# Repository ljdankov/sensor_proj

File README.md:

# sensor_proj
The files in here are designed to pull capacitive touch data (and other relevant sensors) from the boards I have been working with (ESP32 and Teensy 3.2).
Files included
  ARDUINO IDE: Teensy 3.2 version, ARDUINO IDE: ESP32 Version, PYTHON Interface
It should be noted that documentation may be somewhat minimal as this repository is mostly for myself and other people I am working with on project

At minimum, note dependencies in the files. The Teensy variant will need the teensy software from: https://www.pjrc.com/teensy/teensyduino.html
The esp32 variant will require the Arduino IDE software from:
https://github.com/espressif/arduino-esp32

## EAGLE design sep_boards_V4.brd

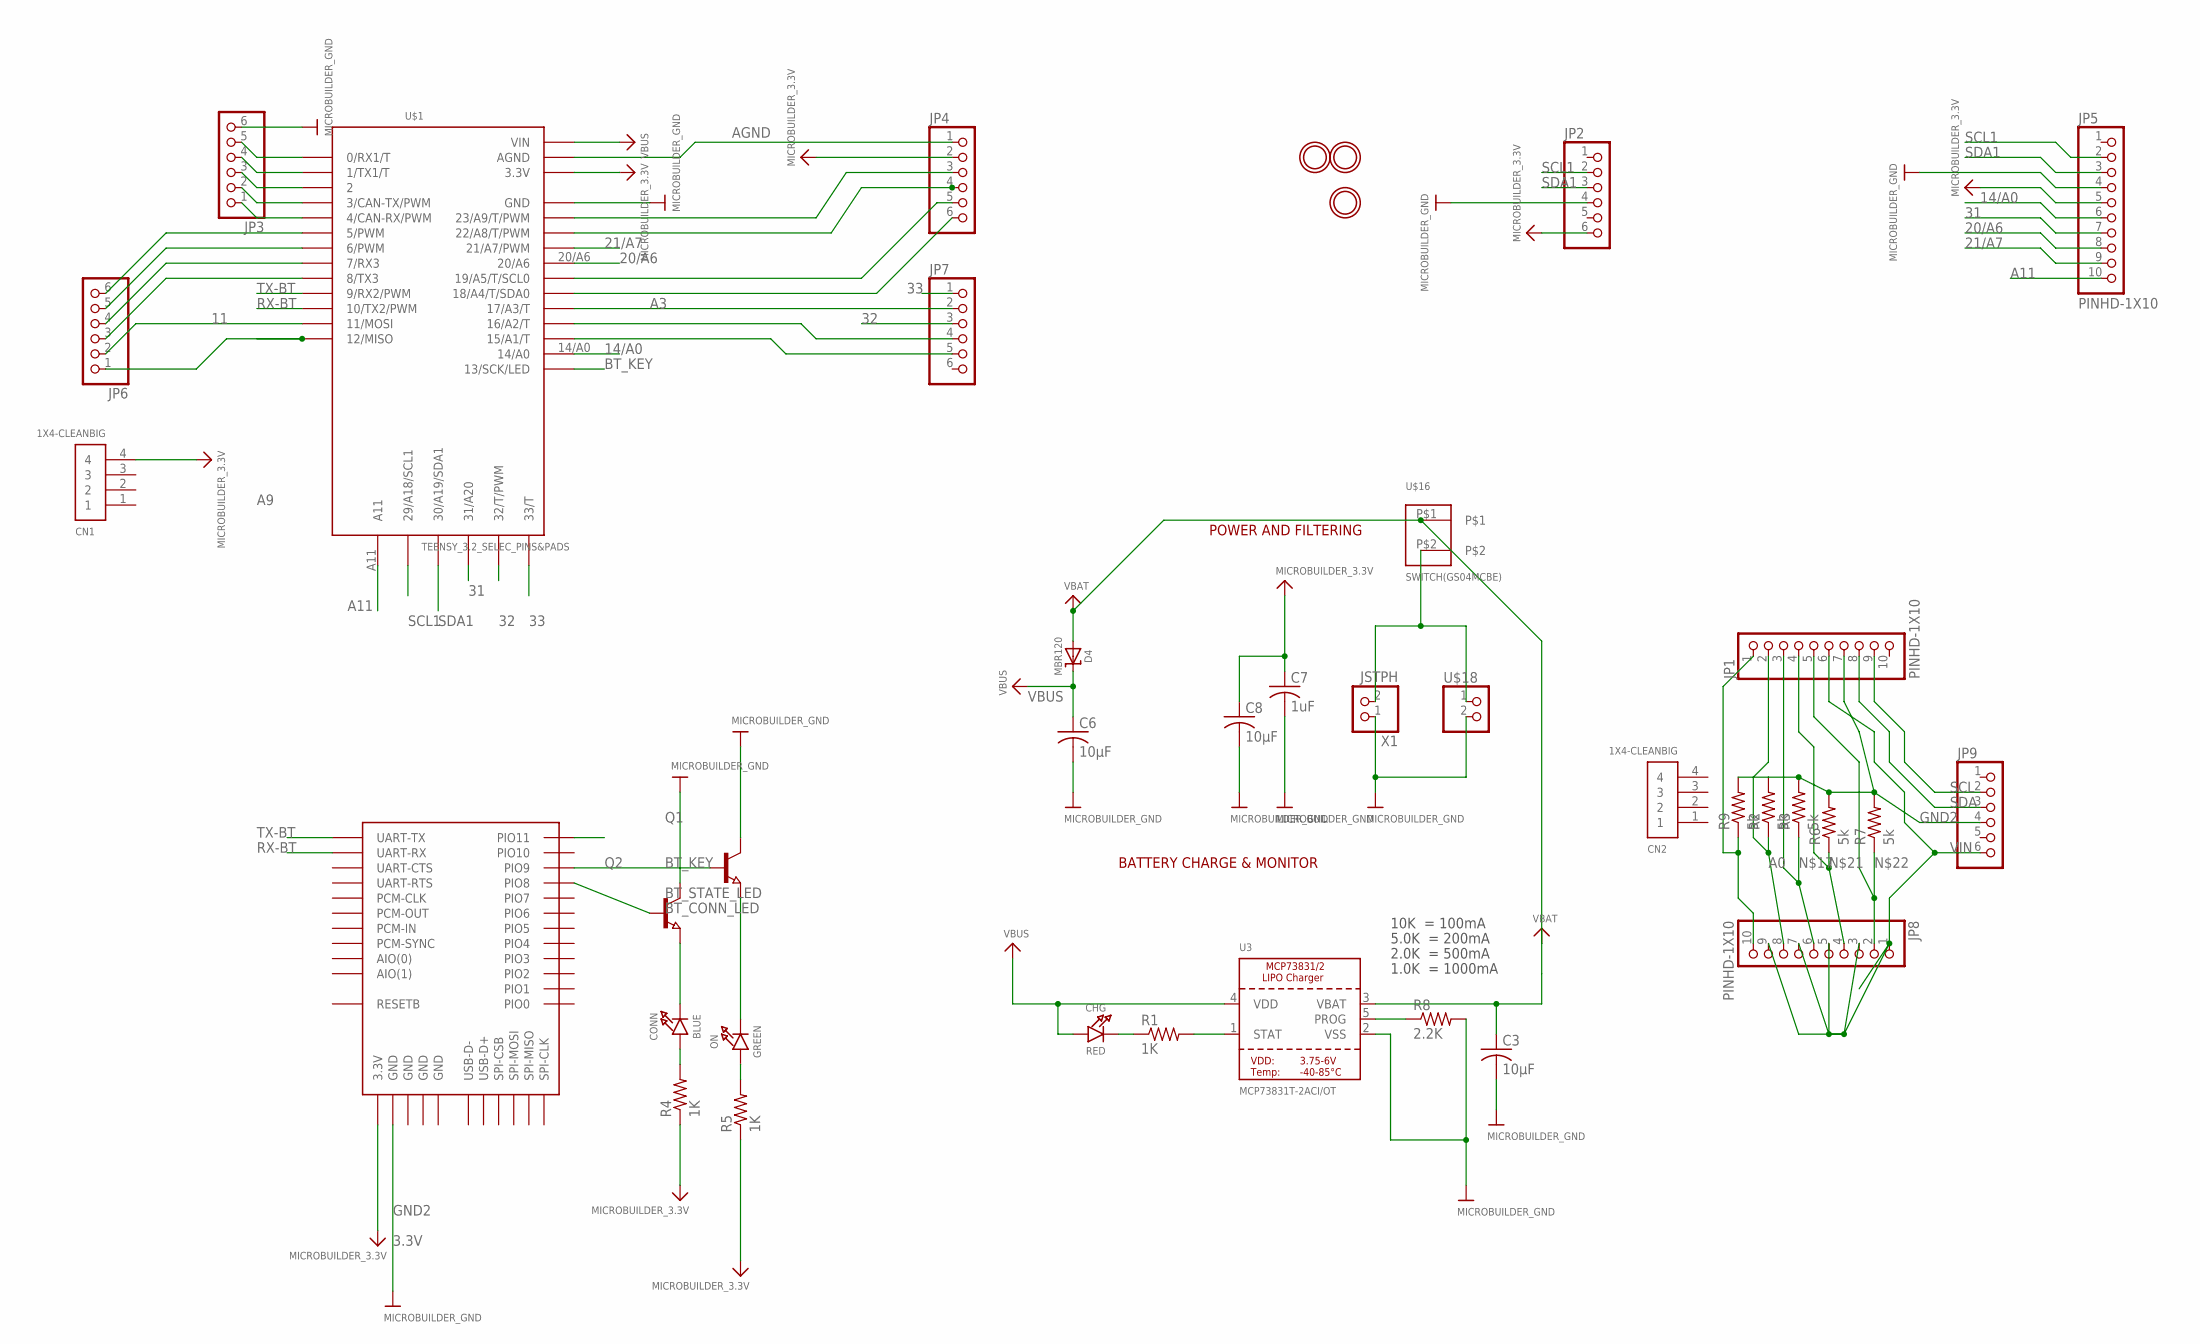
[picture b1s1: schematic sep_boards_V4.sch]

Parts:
C3, C6, C8: 10µF; C0805
C7: 1uF; C0805
CHG: RED; CHIPLED_0805_NOOUTLINE
CN1, CN2: 1X4-CLEANBIG; 1X04-CLEANBIG
CONN: BLUE; CHIPLED_0805_NOOUTLINE
D4: MBR120; SOD-123
JP1, JP5, JP8: PINHD-1X10; 1X10-BIG
JP2: PINHD-1X6CLEAN; 1X06-CLEAN
JP3, JP4, JP6, JP7: PINHD-1X6B; 1X06-BIG
JP9: PINHD-1X6CB; 1X06-CLEANBIG
ON: GREEN; CHIPLED_0805_NOOUTLINE
Q1, Q2: NPN-TRANSISTOR_SOT23; SOT23
R1, R4, R5: 1K; M0805
R2, R3, R6, R7, R9: 5k; M0805
R8: 2.2K; M0805
U3: MCP73831T-2ACI/OT; SOT23-5
U$1: TEENSY_3.2_SELEC_PINS&PADS; TEENSY_3.0-3.2SELEC_PINS&_PADS
U$2: BTM400_6B
U$16: SWITCH(GS04MCBE)
U$18: PINHD-1X2; 1X02
U$22, U$23, U$32: MOUNTINGHOLE2.5; MOUNTINGHOLE_2.5_PLATED
X1: JSTPH; JSTPH2

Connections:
3.3V: C7.1, C8.1, CN1.4, JP2.6, JP4.2, JP5.5, R4.1, R5.1, U$1.3.3V, U$2.3.3V
11: JP6.2, U$1.11 (11/MOSI)
14/A0: JP5.6, U$1.14/A0
20/A6: JP5.8, U$1.20/A6
21/A7: JP5.9, U$1.21/A7 (21/A7/PWM)
31: JP5.7, U$1.31 (31/A20)
32: JP7.3, U$1.32 (32/T/PWM)
33: JP7.1, U$1.33 (33/T)
A0: JP1.2, JP8.8, R2.1
A3: JP7.2, U$1.17/A3 (17/A3/T)
A8: JP4.4, U$1.22/A8 (22/A8/T/PWM)
A9: JP4.3, U$1.23/A9 (23/A9/T/PWM)
A11: JP5.10, U$1.A11
AGND: JP4.1, U$1.AGND
BT_CONN_LED: Q2.1 (B), U$2.PIO(8) (PIO8)
BT_KEY: U$1.13 (13/SCK/LED), U$2.PIO(11) (PIO11)
BT_STATE_LED: Q1.1 (B), U$2.PIO(9) (PIO9)
GND2: C3.2, C6.2, C7.2, C8.2, JP1.7, JP2.4, JP3.6, JP5.4, JP9.4, Q1.3 (C), Q2.3 (C), R2.2, R3.2, R6.2, R7.2, R8.2, R9.2, U3.2 (VSS), U$1.GND, U$2.GND@1 (GND), U$2.GND@2 (GND), U$2.GND@3 (GND), U$2.GND@4 (GND), U$18.2, X1.1
unnamed: CONN.A, R4.2
unnamed: ON.A, R5.2
unnamed: JP3.1, U$1.4 (4/CAN-RX/PWM)
unnamed: JP3.2, U$1.3 (3/CAN-TX/PWM)
unnamed: ON.C, Q1.2 (E)
unnamed: CONN.C, Q2.2 (E)
unnamed: JP3.3, U$1.2
unnamed: JP3.4, U$1.1 (1/TX1/T)
unnamed: JP3.5, U$1.0 (0/RX1/T)
unnamed: JP7.4, U$1.16/A2 (16/A2/T)
unnamed: JP6.6, U$1.5 (5/PWM)
unnamed: JP6.5, U$1.6 (6/PWM)
unnamed: JP6.4, U$1.7 (7/RX3)
unnamed: JP6.3, U$1.8 (8/TX3)
unnamed: JP6.1, U$1.12 (12/MISO)
unnamed: JP1.1, JP8.10, R9.1
unnamed: JP1.3, JP8.6, R3.1
unnamed: JP4.5, U$1.19/A5 (19/A5/T/SCL0)
unnamed: JP4.6, U$1.18/A4 (18/A4/T/SDA0)
unnamed: JP7.5, U$1.15/A1 (15/A1/T)
unnamed: JP1.4, JP8.4, R6.1
unnamed: JP1.5, JP8.2, R7.1
unnamed: CHG.C, R1.1
unnamed: R1.2, U3.1 (STAT)
unnamed: R8.1, U3.5 (PROG)
RX-BT: U$1.10 (10/TX2/PWM), U$2.UART-RX
SCL: JP1.9, JP9.2
SCL1: JP2.2, JP5.2, U$1.29 (29/A18/SCL1)
SDA: JP1.8, JP9.3
SDA1: JP2.3, JP5.3, U$1.30 (30/A19/SDA1)
TX-BT: U$1.9 (9/RX2/PWM), U$2.UART-TX
VBAT: U$16.P$2, U$18.1, X1.2
VBAT2: C3.1, D4.A, U3.3 (VBAT), U$16.P$1
VBUS: C6.1, CHG.A, D4.C, U3.4 (VDD), U$1.VIN
VIN: JP1.6, JP8.1, JP8.3, JP8.5, JP8.7, JP8.9, JP9.6

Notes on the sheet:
POWER AND FILTERING
10K = 100mA
5.0K = 200mA
2.0K = 500mA
1.0K = 1000mA
BATTERY CHARGE & MONITOR

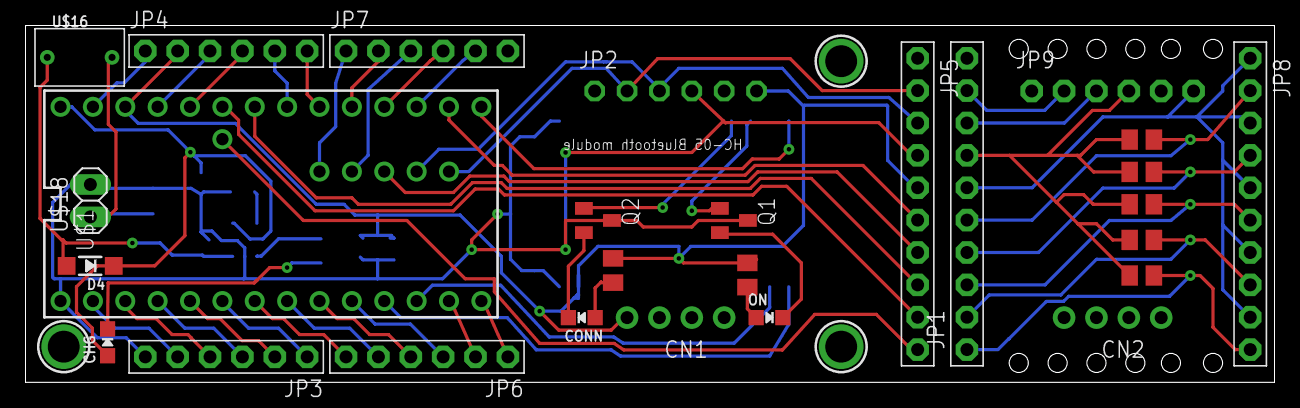
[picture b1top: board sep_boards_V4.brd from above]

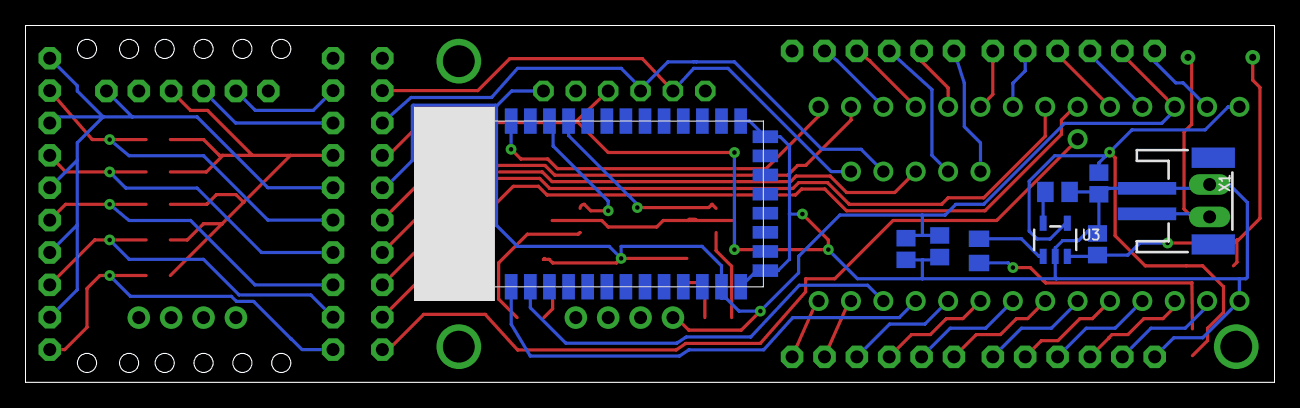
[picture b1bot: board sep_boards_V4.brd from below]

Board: 2 copper layers, 98.0 x 28.0 mm, 39 parts (9 on the bottom side), 53 nets.

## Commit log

2018-06-18 Create python interface
2018-06-27 Update python interface

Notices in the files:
parts and their libraries:
microbuilder: This work is placed in the public domain, and may be freely used for commercial and non-commercial work with the following conditions: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
